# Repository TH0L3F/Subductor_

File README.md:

#Subductor

Une machine pour le laboratoire de sciences naturelles de L'université de Lille (Cité scientifique) SN5

## Objectif

Le subductor a pour objectif de subducter ... Bon c'est pas super clair comme ça donc je vais faire mieux:
L'objectif est de tirer un bloc de sable avec un tissus (ici un morceau de voile de bateau) par le dessous afin de simuler des mouvements tectoniques et leurs effets sur des blocs de sable.

### Matériel

Pour se faire est mis à la disposition de l'utilisateur un boitier possédant un écran lcd 4 lignes 20 caractères par lignes ainsi qu'un encodeur rotatif avec un bouton inclus.

### Préparation

Au démarrage de la machine il faut avec le mode Incrémental faire deux tours de aux tapis autour de la tige d'enroulement puis redemarrer la machine pour commencer à l'utiliser.
Le nombre d'enroulement du tapis n'étant pas mesurer : il s'agit de la seule manière de connaître sa position eu démarrage puis de la calculer au cours du fonctionnement de la machine.

### Mode

Dans un premier temps il faut choisir un mode entre:
-Continu : Sélection de la vitesse de déplacement du tapis.
-Incrémental : Sélection de la position voulue du tapis puis déplacement de celui-ci.

Pour passer d'un mode à l'autre il faut éteindre puis allumer la machine (Choix seulement au démarrage).

#### Continu

Choix de la vitesse avec l'encodeur puis appuie sur le bouton 2 secondes pour mettre en mouvement la machine.
Lors d'un changement de vitesse en bougeant l'encodeur il faut appuyer sur le bouton pour confirmer la modification et qu'elle devienne effective.

#### Incrémental

Choix de la position avec l'encodeur puis appuie sur le bouton 2 secondes pour mettre en mouvement la machine.
A chaques changement de position il faut appuyer à nouveau sur le bouton pendant 2 secondes sur le bouton de l'encodeur pour que le changement soit pris en compte.

## Electronique

Du point de vue électronique une carte permet de connecter chaques composants via des connecteurs JST-XH afin de limiter au maximum la possibilité de déconnexion dû aux vibrations ou au temps. Les composants sont tous connecter à un atmega328p cadencé à 16MHz. L'écran en I2C et l'encodeur sur des pin digital. Le driver de moteur pas à pas sur des pins digital lui aussi.

## Programmation

Pour programmer il faut utiliser un programmateur spécifique et le connecteur correspondant sur la carte. Le programmateur est le même que le programmateur du projet Slicor. Une petite fléche permet sur la carte et le connecteur du programmateur permet de détromper le sens de connexion. Ensuite via l'IDE arduino il est possible de mettre le bootloader ("carte : arduino uno", "programmateur : TINYasISP" puis "burn bootloader") il est nécessaire de mettre le bootloader si la puce n'en a pas déjà. Ensuite avec l'option "programmer via un programmateur" il est possible de téléverser le programmer dans le microcontrôleur. 

ATTENTION: Avec le programmeteur mis à dispositon une erreur survient dans certaine condition. Si un timeout est émis par le programmateur une solution est d'enlever ou d'ajouter des delay(1) dans la partie setup du programme. (Si une meilleure solution existe je suis preneur).

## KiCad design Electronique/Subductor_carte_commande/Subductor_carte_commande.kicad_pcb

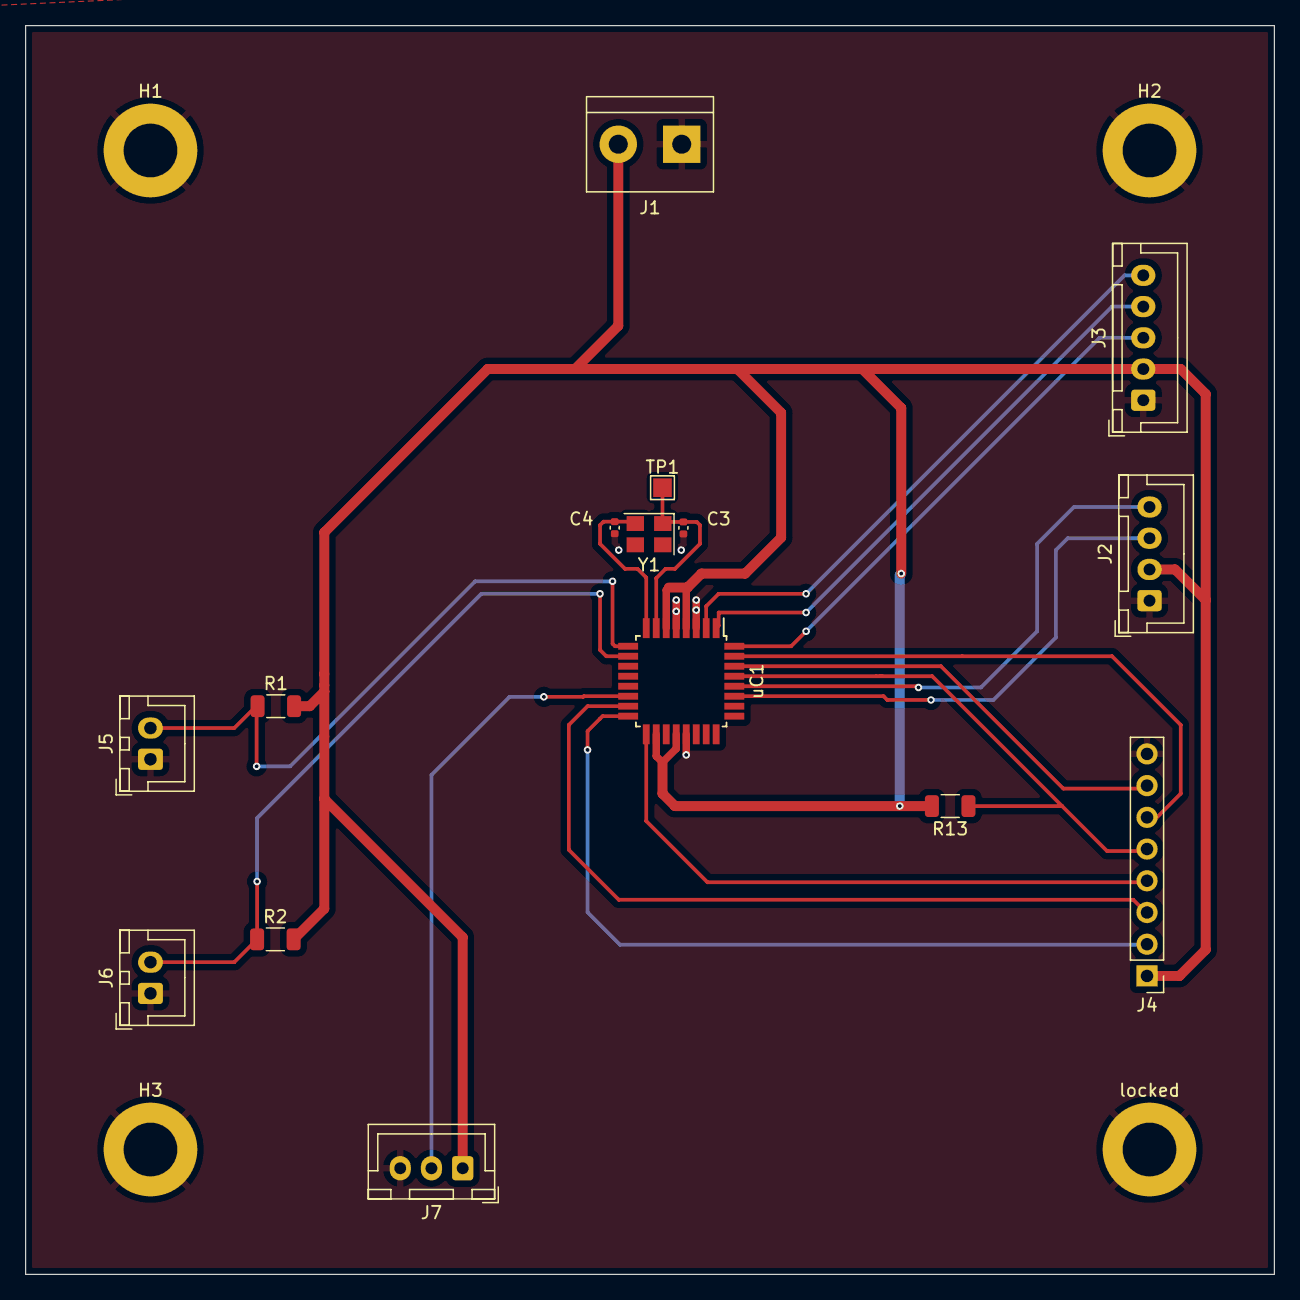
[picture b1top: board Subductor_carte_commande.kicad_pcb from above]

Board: 4 copper layers, 100.0 x 100.0 mm, 19 parts (0 on the bottom side), 18 nets.

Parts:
C3, C4: 22p; C_0402_1005Metric
H1, H2, H3: MountingHole_Pad; MountingHole_4.3mm_M4_DIN965_Pad
J1: Connecteur_Alim; TerminalBlock_bornier-2_P5.08mm
J2: Connecteur_ecran; JST_XH_B4B-XH-A_1x04_P2.50mm_Vertical
J3: Conn_encodeur_rotatif; JST_XH_B5B-XH-A_1x05_P2.50mm_Vertical
J4: Connecteur_Prog; PinHeader_1x08_P2.54mm_Vertical
J5: Connecteur_bouton_1; JST_XH_B2B-XH-A_1x02_P2.50mm_Vertical
J6: Connecteur_bouton_2; JST_XH_B2B-XH-A_1x02_P2.50mm_Vertical
J7: Conn_01x03_Female; JST_XH_B3B-XH-A_1x03_P2.50mm_Vertical
R1, R2: 10k; R_1206_3216Metric
R13: 100k; R_1206_3216Metric
TP1: TestPoint; TestPoint_Pad_1.5x1.5mm
Y1: 16MHz; Crystal_SMD_3225-4Pin_3.2x2.5mm
locked: MountingHole_Pad; MountingHole_4.3mm_M4_DIN965_Pad
uC1: ATmega328-A; TQFP-32_7x7mm_P0.8mm

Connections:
+5V: J1.2, J2.2, J3.2, J4.1, J7.1, R1.2, R2.2, R13.2, uC1.4 (VCC), uC1.6 (VCC), uC1.18 (AVCC), uC1.20 (AREF)
BUZZER: J7.2, uC1.14 (PB2)
Bouton1: J5.2, R1.1, uC1.9 (PD5)
Bouton2: J6.2, R2.1, uC1.10 (PD6)
CLK: J3.5, uC1.2 (PD4)
DT: J3.4, uC1.1 (PD3)
GND: C3.2, C4.2, H1.1, H2.1, H3.1, J1.1, J2.1, J3.1, J4.8, J5.1, J6.1, J7.3, locked.1, uC1.3 (GND), uC1.5 (GND), uC1.21 (GND)
MISO: J4.2, uC1.16 (PB4)
MOSI: J4.3, uC1.15 (PB3)
unnamed: C3.1, TP1.1, Y1.1, uC1.7 (XTAL1/PB6)
unnamed: C4.1, Y1.2, uC1.8 (XTAL2/PB7)
RST: J4.5, R13.1, uC1.29 (~RESET/PC6)
SCK: J4.4, uC1.17 (PB5)
SCL: J2.4, uC1.28 (PC5)
SDA: J2.3, uC1.27 (PC4)
SW: J3.3, uC1.32 (PD2)
UART RX: J4.7, uC1.30 (PD0)
UART TX: J4.6, uC1.31 (PD1)

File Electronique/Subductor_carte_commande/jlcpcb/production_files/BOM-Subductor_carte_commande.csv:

Comment,Designator,Footprint,LCSC
16MHz,Y1,Crystal_SMD_3225-4Pin_3.2x2.5mm,C13738
ATmega328-A,uC1,TQFP-32_7x7mm_P0.8mm,C14877
22p,"C3,C4",C_0402_1005Metric,C1555
100k,R13,R_1206_3216Metric,C17900
10k,"R1,R2",R_1206_3216Metric,C17902
Connecteur_Prog,J4,PinHeader_1x08_P2.54mm_Vertical,
Conn_encodeur_rotatif,J3,JST_XH_B5B-XH-A_1x05_P2.50mm_Vertical,
Connecteur_bouton_1,J5,JST_XH_B2B-XH-A_1x02_P2.50mm_Vertical,
Connecteur_ecran,J2,JST_XH_B4B-XH-A_1x04_P2.50mm_Vertical,
Connecteur_Alim,J1,TerminalBlock_bornier-2_P5.08mm,
MountingHole_Pad,H1,MountingHole_4.3mm_M4_DIN965_Pad,
MountingHole_Pad,H4,MountingHole_4.3mm_M4_DIN965_Pad,
Connecteur_bouton_2,J6,JST_XH_B2B-XH-A_1x02_P2.50mm_Vertical,
MountingHole_Pad,H3,MountingHole_4.3mm_M4_DIN965_Pad,
MountingHole_Pad,H2,MountingHole_4.3mm_M4_DIN965_Pad,
TestPoint,TP1,TestPoint_Pad_1.5x1.5mm,
Conn_01x03_Female,J7,JST_XH_B3B-XH-A_1x03_P2.50mm_Vertical,

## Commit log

2023-05-21 maj new repo
